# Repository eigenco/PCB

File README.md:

# PCB

WARNING! These boards are still very early models and likely contain bugs. They've been observed to work with either no modification or with minor modification (like adding a pullup resistor) during the soldering stage, but be aware that they might not work directly "out of the box" for you or present a risk of something breaking.

Minimal 8088 8 bit ISA board

This board is slightly custom. Signals INTAK and INT have been routed through DRQ2 and DACK2 to allow external PIC-board in the BUS, equally HLDA and HOLD have been routed through DRQ3 and DACK3 to allow external DMAC-board in the BUS. These customizations mean that DMA channels 2 and 3 cannot be used normally. The board will boot when RESET jumper is connected being initially disconnected during power-up. There are 3 other jumpers for allowing operation with or without PIC and DMAC. Can boot into DOS with suitable BIOS (v2). Tested with 8 MHz V20.

Minimal Adlib compatible 8 bit ISA board

This board has its own oscillator and thus requires neither CLK or OSC to be present in the BUS.

Minimal OPL3 compatible 8 bit ISA board

This board requires OSC (14.31818 MHz) signal present in the BUS.

Minimal 512 KB 8 bit ISA RAM board

This board is configured to occupy 0x00000-0x7FFFF.

Control 8 bit ISA devices through passive backplane using Raspberry Pi (14.31818 MHz oscillator is included, MEMW/MEMR/IOW/IOR are supported, no IRQ or DMA)

Board with 8259 Programmable Interrupt Controller and 8254 Programmable Interval Timer (there is wrong 74LS93 chip in place of 74LS92 in the picture as I didn't have the correct chip at the moment of testing, 74LS93 is decade divider whereas this board requires octal divider so the PIT ran at slightly lower frequence in this test than normally).

Example of "everything" in a backplane, early video https://www.youtube.com/watch?v=vcOmHcExV3M

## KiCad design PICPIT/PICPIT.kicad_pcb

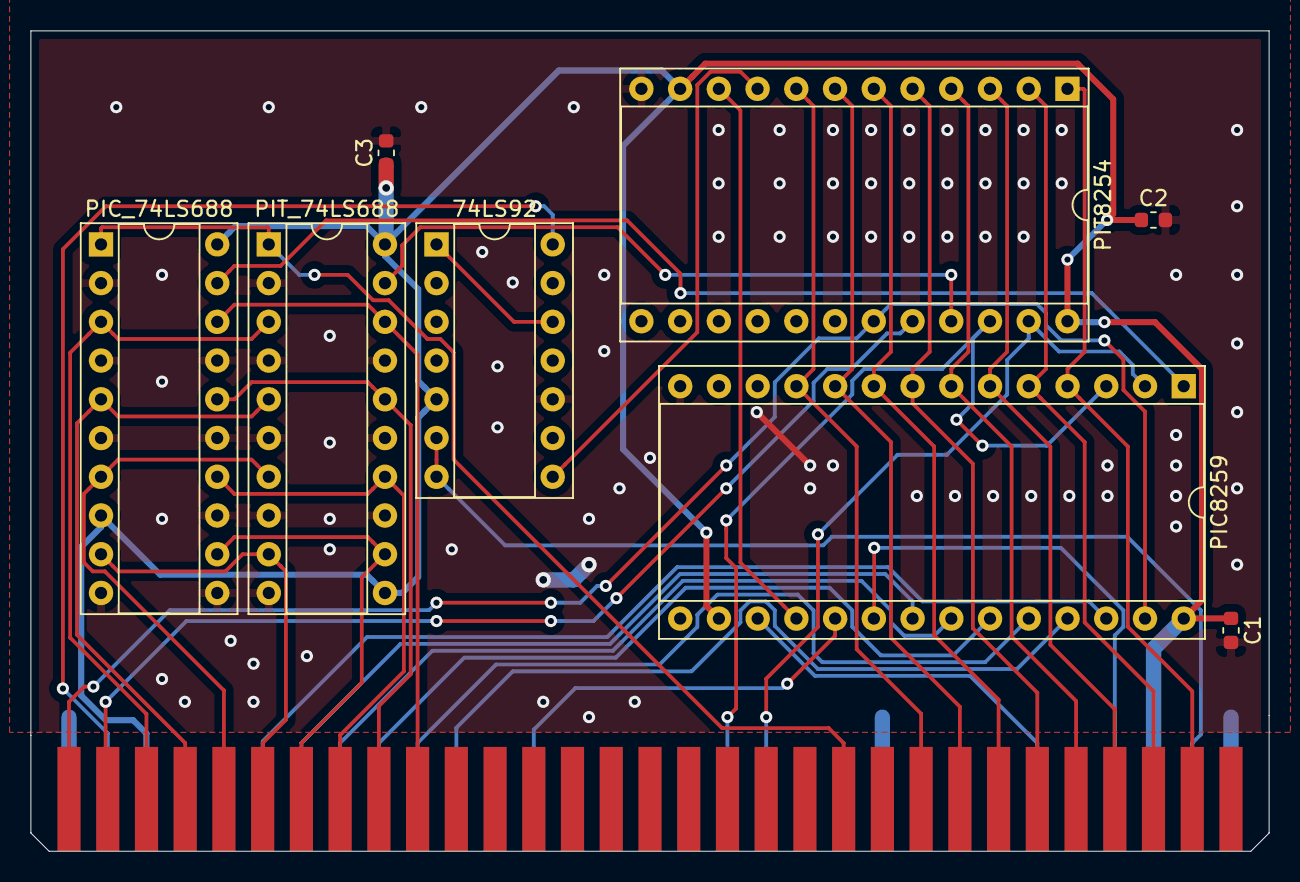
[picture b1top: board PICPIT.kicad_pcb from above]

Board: 2 copper layers, 81.2 x 53.8 mm, 9 parts (0 on the bottom side), 38 nets.

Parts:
74LS92: 74LS92; DIP-14_W7.62mm_Socket
C1, C2, C3: 100nF; C_0603_1608Metric
J4: Bus_ISA_8bit; BUS_PC
PIC8259: Conn_02x14_Counter_Clockwise; DIP-28_W15.24mm_Socket
PIC_74LS688: 74LS688; DIP-20_W7.62mm_Socket
PIT8254: Conn_02x12_Counter_Clockwise; DIP-24_W15.24mm_Socket
PIT_74LS688: 74LS688; DIP-20_W7.62mm_Socket

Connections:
A0: J4.62, PIC8259.27, PIT8254.19
A1: J4.61, PIT8254.20
A2: J4.60, PIC_74LS688.3, PIT_74LS688.3
A3: J4.59, PIC_74LS688.5, PIT_74LS688.5
A4: J4.58, PIC_74LS688.7, PIT_74LS688.7
A5: J4.57, PIC_74LS688.9, PIT_74LS688.9
A6: J4.56, PIC_74LS688.12, PIT_74LS688.12
A7: J4.55, PIC_74LS688.14, PIT_74LS688.14
A8: J4.54, PIC_74LS688.16, PIT_74LS688.16
A9: J4.53, PIC_74LS688.18, PIT_74LS688.18
AEN: J4.42, PIC_74LS688.1, PIT_74LS688.1
CSPIC: PIC8259.1, PIC_74LS688.19
CSPIT: PIT8254.21, PIT_74LS688.19
D0: J4.40, PIC8259.11, PIT8254.8
D1: J4.39, PIC8259.10, PIT8254.7
D2: J4.38, PIC8259.9, PIT8254.6
D3: J4.37, PIC8259.8, PIT8254.5
D4: J4.36, PIC8259.7, PIT8254.4
D5: J4.35, PIC8259.6, PIT8254.3
D6: J4.34, PIC8259.5, PIT8254.2
D7: J4.33, PIC8259.4, PIT8254.1
GND: 74LS92.10, C1.2, C2.2, C3.2, J4.1, J4.10, J4.31, PIC8259.14, PIC_74LS688.2, PIC_74LS688.4, PIC_74LS688.6, PIC_74LS688.10, PIC_74LS688.11, PIC_74LS688.13, PIC_74LS688.15, PIC_74LS688.17, PIT8254.12, PIT_74LS688.2, PIT_74LS688.4, PIT_74LS688.6, PIT_74LS688.8, PIT_74LS688.10, PIT_74LS688.13, PIT_74LS688.15, PIT_74LS688.17
INT: J4.6, PIC8259.17
INTAK: J4.26, PIC8259.26
IOR: J4.14, PIC8259.3, PIT8254.22
IOW: J4.13, PIC8259.2, PIT8254.23
IRQ0: PIC8259.18, PIT8254.10
IRQ1: J4.25, PIC8259.19
IRQ2: J4.4, PIC8259.20
IRQ4: J4.24, PIC8259.22
IRQ5: J4.23, PIC8259.23
IRQ6: J4.22, PIC8259.24
IRQ7: J4.21, PIC8259.25
OSC: 74LS92.14, J4.30
OSC1: 74LS92.8, PIT8254.9
Q0: 74LS92.1, 74LS92.12
RESET: 74LS92.6, 74LS92.7, J4.2
VCC: 74LS92.5, C1.1, C2.1, C3.1, J4.3, J4.29, PIC8259.16, PIC8259.28, PIC_74LS688.8, PIC_74LS688.20, PIT8254.11, PIT8254.24, PIT_74LS688.11, PIT_74LS688.20

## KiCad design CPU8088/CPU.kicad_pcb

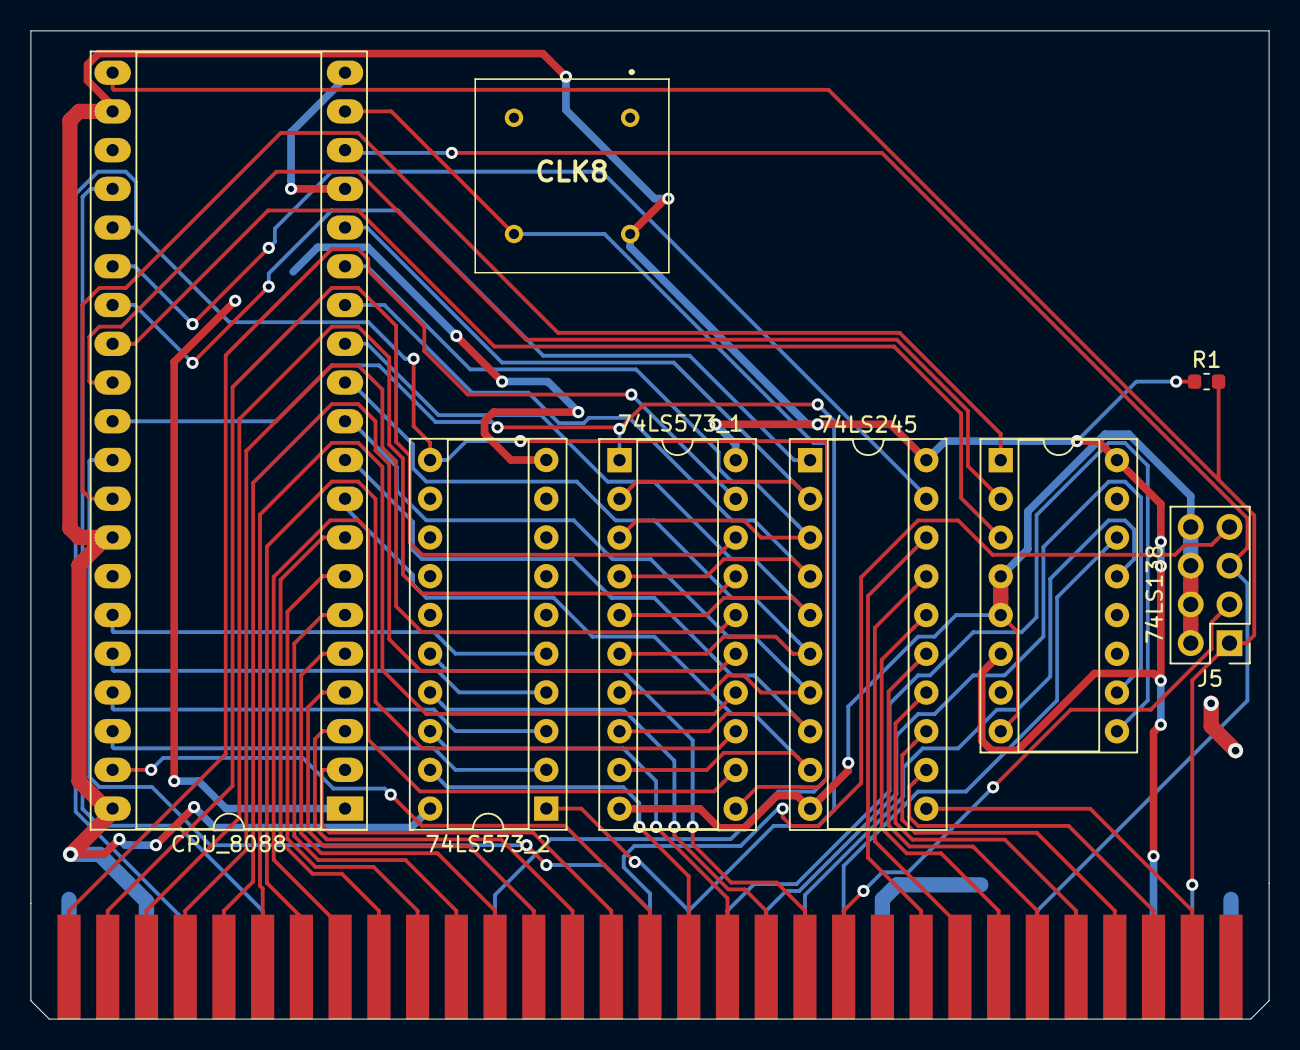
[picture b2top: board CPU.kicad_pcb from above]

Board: 2 copper layers, 81.2 x 64.8 mm, 9 parts (0 on the bottom side), 59 nets.

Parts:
74LS138: Conn_02x08_Counter_Clockwise; DIP-16_W7.62mm_Socket
74LS245, 74LS573_1, 74LS573_2: Conn_02x10_Counter_Clockwise; DIP-20_W7.62mm_Socket
CLK8: ACH-14.31818MHZ-EK; ACH16000MHZEK
CPU_8088: Conn_02x20_Counter_Clockwise; DIP-40_W15.24mm_Socket_LongPads
J4: Bus_ISA_8bit; BUS_PC
J5: Conn_02x04_Odd_Even; PinHeader_2x04_P2.54mm_Vertical
R1: 1k; R_0603_1608Metric

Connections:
A0: 74LS573_1.19, J4.62
A1: 74LS573_1.18, J4.61
A2: 74LS573_1.17, J4.60
A3: 74LS573_1.16, J4.59
A4: 74LS573_1.15, J4.58
A5: 74LS573_1.14, J4.57
A6: 74LS573_1.13, J4.56
A7: 74LS573_1.12, J4.55
A8: CPU_8088.8, J4.54
A9: CPU_8088.7, J4.53
A10: CPU_8088.6, J4.52
A11: CPU_8088.5, J4.51
A12: CPU_8088.4, J4.50
A13: CPU_8088.3, J4.49
A14: CPU_8088.2, J4.48
A15: CPU_8088.39, J4.47
A16: 74LS573_2.19, J4.46
A17: 74LS573_2.18, J4.45
A18: 74LS573_2.17, J4.44
A19: 74LS573_2.16, J4.43
AD0: 74LS245.2, 74LS573_1.2, CPU_8088.16
AD1: 74LS245.3, 74LS573_1.3, CPU_8088.15
AD2: 74LS245.4, 74LS573_1.4, CPU_8088.14
AD3: 74LS245.5, 74LS573_1.5, CPU_8088.13
AD4: 74LS245.6, 74LS573_1.6, CPU_8088.12
AD5: 74LS245.7, 74LS573_1.7, CPU_8088.11
AD6: 74LS245.8, 74LS573_1.8, CPU_8088.10
AD7: 74LS245.9, 74LS573_1.9, CPU_8088.9
AEN: J4.42, J5.3
ALE: 74LS573_1.11, 74LS573_2.11, CPU_8088.25, J4.28
A_16: 74LS573_2.2, CPU_8088.38
A_17: 74LS573_2.3, CPU_8088.37
A_18: 74LS573_2.4, CPU_8088.36
A_19: 74LS573_2.5, CPU_8088.35
CLK: CLK8.5, CPU_8088.19, J4.20
D0: 74LS245.18, J4.40
D1: 74LS245.17, J4.39
D2: 74LS245.16, J4.38
D3: 74LS245.15, J4.37
D4: 74LS245.14, J4.36
D5: 74LS245.13, J4.35
D6: 74LS245.12, J4.34
D7: 74LS245.11, J4.33
DEN: 74LS245.19, CPU_8088.26
DTR: 74LS245.1, CPU_8088.27
GND: 74LS138.4, 74LS138.5, 74LS138.8, 74LS245.10, 74LS573_1.10, 74LS573_2.10, CLK8.4, CPU_8088.1, CPU_8088.17, CPU_8088.20, CPU_8088.23, J4.1, J4.10, J4.31, J5.2, J5.4, J5.6, J5.8
HLDA: 74LS573_1.1, 74LS573_2.1, CPU_8088.30, J4.15
HOLD: CPU_8088.31, J4.16, J5.7
INT: CPU_8088.18, J4.6, J5.5
INTAK: CPU_8088.24, J4.26
IOM: 74LS138.3, CPU_8088.28
IOR: 74LS138.9, J4.14
IOW: 74LS138.10, J4.13
MEMR: 74LS138.13, J4.12
MEMW: 74LS138.14, J4.11
RD: 74LS138.1, CPU_8088.32
RESET: CPU_8088.21, J4.2, J5.1, R1.2
VCC: 74LS138.6, 74LS138.16, 74LS245.20, 74LS573_1.20, 74LS573_2.20, CLK8.8, CPU_8088.22, CPU_8088.33, CPU_8088.40, J4.3, J4.29, R1.1
WR: 74LS138.2, CPU_8088.29

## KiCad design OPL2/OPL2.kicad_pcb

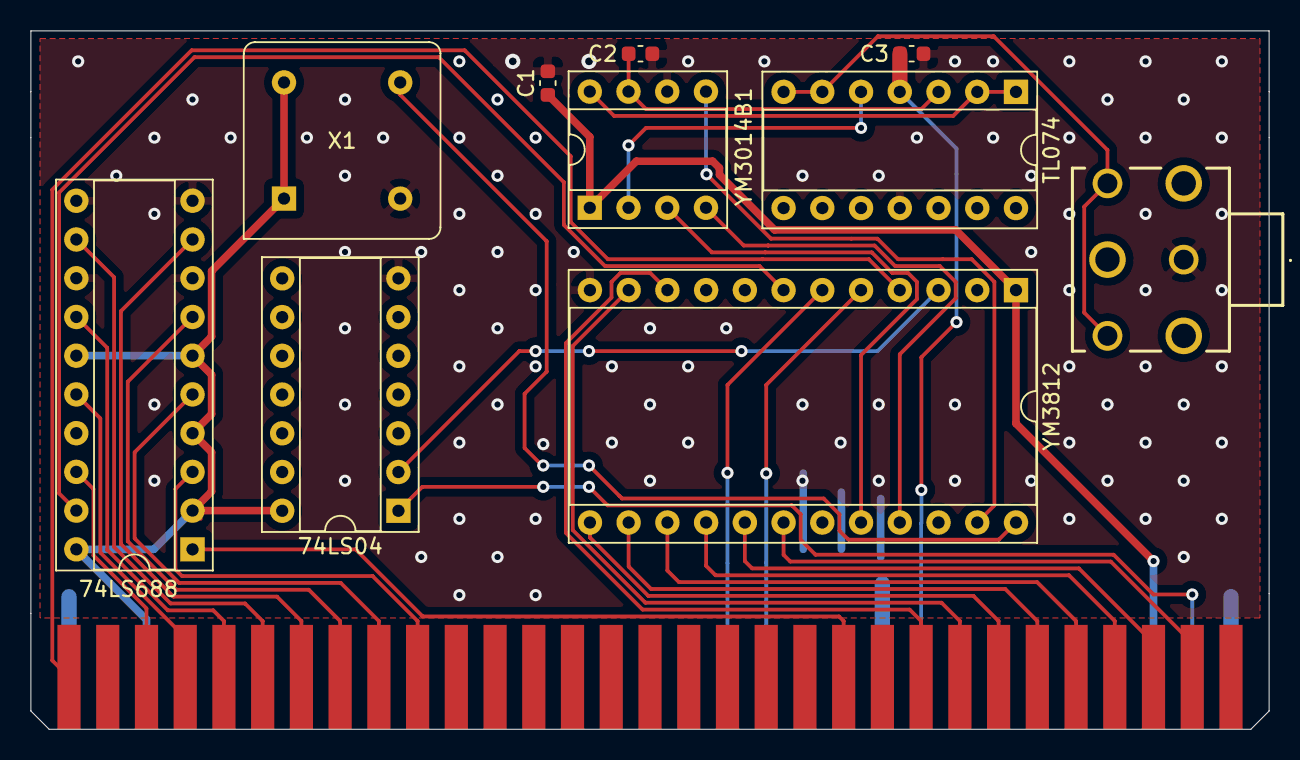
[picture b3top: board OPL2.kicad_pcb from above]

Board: 2 copper layers, 81.2 x 45.8 mm, 11 parts (0 on the bottom side), 34 nets.

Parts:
74LS04: 74LS04; DIP-14_W7.62mm_Socket
74LS688: 74LS688; DIP-20_W7.62mm_Socket
C1, C2, C3: 10uF; C_0603_1608Metric
J3: Conn_02x03_Counter_Clockwise; STX31003N
J4: Bus_ISA_8bit; BUS_PC
TL074: TL074; DIP-14_W7.62mm_Socket
X1: CXO_DIP8; Oscillator_DIP-8
YM3014B1: Conn_02x04_Counter_Clockwise; DIP-8_W7.62mm_Socket
YM3812: Conn_02x12_Counter_Clockwise; DIP-24_W15.24mm_Socket

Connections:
A0: J4.62, YM3812.4
A2: 74LS688.18, J4.60
A3: 74LS688.16, J4.59
A4: 74LS688.14, J4.58
A5: 74LS688.12, J4.57
A6: 74LS688.9, J4.56
A7: 74LS688.7, J4.55
A8: 74LS688.5, J4.54
A9: 74LS688.3, J4.53
AEN: 74LS688.1, J4.42
CLK358: X1.5, YM3812.24
D0: J4.40, YM3812.10
D1: J4.39, YM3812.11
D2: J4.38, YM3812.13
D3: J4.37, YM3812.14
D4: J4.36, YM3812.15
D5: J4.35, YM3812.16
D6: J4.34, YM3812.17
D7: J4.33, YM3812.18
DAC_CLK: YM3014B1.5, YM3812.23
DAC_DATA: YM3014B1.4, YM3812.21
DAC_SYNC: YM3014B1.3, YM3812.20
GND: 74LS04.7, 74LS688.8, 74LS688.10, 74LS688.11, 74LS688.13, 74LS688.17, C1.2, C2.2, C3.2, J3.1, J4.1, J4.10, J4.31, TL074.11, X1.4, YM3014B1.6, YM3812.12
MP: TL074.1, TL074.2, YM3014B1.8
OUT: J3.2, J3.5, TL074.6, TL074.7
RB: C2.1, TL074.3, YM3014B1.7
RESET: 74LS04.1, J4.2
ToBUFF: TL074.5, YM3014B1.2
VCC: 74LS04.14, 74LS688.2, 74LS688.4, 74LS688.6, 74LS688.15, 74LS688.20, C1.1, J4.3, J4.29, X1.1, X1.8, YM3014B1.1, YM3812.1
VP: C3.1, J4.9, TL074.4
~CS: 74LS688.19, YM3812.7
~IOR: J4.14, YM3812.6
~IOW: J4.13, YM3812.5
~RESET: 74LS04.2, YM3812.3

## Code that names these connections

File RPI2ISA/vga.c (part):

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#include <unistd.h>

#define LA	23
#define IOW	25
#define IOR	11
#define MEMR	9
#define MEMW	10
#define RESET	22

#define D0	27
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  wiringPiSetupGpio();

  pinMode(LA, OUTPUT); digitalWrite(LA, 0);
  pinMode(IOW, OUTPUT);
  pinMode(IOR, OUTPUT);
  pinMode(MEMW, OUTPUT);
  pinMode(MEMR, OUTPUT);
  pinMode(RESET, OUTPUT);
  digitalWrite(RESET, 1); usleep(100000);
  digitalWrite(RESET, 0); usleep(100000);
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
